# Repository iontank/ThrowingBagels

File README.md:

# ThrowingBagels
**ThrowingBagels** is a modernization of the [LEDScape](https://github.com/osresearch/LEDscape) software package. ThrowingBagels a LED driver software package for the ~~bagelbone~~ BeagleBone Black, which drives LEDs from UDP packets you yeet at it over the network, or from your own custom software.

You can use ThrowingBagels to drive up to 32 channels of individual LED strips, up to 512 LEDs per channel. Any addressable LEDs that support the WS or SK control protocols should work (WS2812, SK6812, mainly). This should work on any BeagleBone Black, running Debian Buster. 

## What's it For?

Like we said, you can drive up to 32 channels of individual LED strips, up to 512 LEDs per channel. We've used versions of this software do build things like:

<br>
<br>
<br>
If you want LEDs to blink pretty, this gives you a powerful way to control them. All images above via [Iontank](https://www.facebook.com/Iontank)'s Facebook. See also the [Iontank website](http://iontank.com).

## Installing
`curl https://raw.githubusercontent.com/iontank/ThrowingBagels/master/install.sh | bash`

This script will:

* Clone ThrowingBagels into `/opt/ThrowingBagels`
* Grant ownership of that directory to the current user (probably `debian`)
* Build the code
* Provision the Beaglebone
  * Create the leds.config file
  * Change the hostname
  * Update the `/boot/uEnv.txt` to disable HDMI and audio (we need those GPIO pins)
  * Install, but not enable, the systemd services for core applications

### Running as Services
The primary use case is going to be running this as a UDP listener, but there are a few options for running services.

The first is `bagel-launcher.service`, which simply installs the firmware and configures GPIO at boot. It's potentially useful for testing if you plan to interactively run your own software.

The second is `multidemo.service`, which runs the multidemo application (see below).

The third is the main application, `led-udp.service`, which runs the LED UDP RX program, and is the primary tool you'll likely use to control LEDs.

After install, all of these services will be installed, but none of them will be enabled.

#### Enable the Appropriate Service
For your usecase, you'll need to `sudo systemctl enable $SERVICE`, where `$SERVICE` is one of the above. You can then `sudo systemctl start $SERVICE`.

## Included Application
### PRU Firmware
The main driver of everything is the PRU Firmware, `ledscape.asm`. This is what drives the GPIO channels to activate the LEDs.

### Demo Applications
For the purposes of testing, iterating, and diagnosing hardware issues, there are several included demo applications.

* `bin/smoke`(`src/demos/smoke_test.c`): a simple smoke test application which sets the LEDs to a "soft-white" for ten seconds, and then back to black. It is the "hello world" of ThrowingBagels applications. (We don't go to full white, because that can overload many power supplies/distribution boards)
* `bin/pru_status`(`src/ledscape/pru_status.c`): a simple tool which checks the status of the PRU firmware.
* `bin/multidemo`(`src/demos/multidemo.c`): a complex and highly configurable suite of animations which run right on the BeagleBone, useful for demonstrating lighting effects without network connectivity. Great "pitch tool" to prove hardware concepts.

### LED UDP RX
The primary application, and what drives the core use-case of this software stack, is the `bin/led-udp-rx` tool (`src/net/udp-rx.c`). This tool listens on a port (default: `9999`) for frame data. This allows a powerful "render machine" to run elsewhere on the network, and send frame data to an arbitrary number of ThrowingBagels instances. See [LED UDP RX](src/net/README.md) for more details.

## Running
Included is a `launcher` script. This script configures the GPIO, deploys the firmware, and then, optionally, launches a requested binary. E.g., `./launcher bin/led-udp-rx`, would launch the LED UDP RX tool on port 9999, using `leds.config` as the source for our led configuration.

### On Configuration
Many of the tools, like `led-udp-rx` and `multidemo`, expect an LED configuration to be supplied. By default, they check `leds.config`, but they both take a command line flag to change that. The file MUST be a single line, in this format:

`number of channels,length of strips,number of bytes`

e.g.:

`32,100,4`: this would drive 32 channels of output, for strips 100 pixels long, and expects each LED to need 4 bytes (an RGBW LED). For LED UDP RX, this also sets the expected packet size- each packet should contain 50 pixels for all 32 channels (see [the UDP RX Readme](src/net/README.md) for more details).

`scripts/provision` will also prompt you for this information during the install.

## Your own ThrowingBagles software
To build your own application running on the BeagleBone, you must include two files. First, you need to include `ledstrips.h` into your C code, and you must include a LUT: either `gamma8.h` (recommended), `linear.h`, or your own custom LUT.

From there, you need to flatten your frames into a stripwise structure, e.g. you should be able to access individual pixels using `fb[(y*w)+x]` (that access the pixel at the given x/y coordinate in a 1D version of your framebuffer). See [modes.h](src/demos/modes.h) for examples.

The key methods you'll use are:

* `strip_config* leds_config(char const * filename)`: load a config file and return the strip config
* `int leds_init(strip_config *cfg)`: give a strip config, this connects to the PRU shared memory. Returns `1` on success, `0` on failure
* `void leds_draw(strip_config * cfg, const void * const frame)`: draws `frame` data to the LEDs. This needs to follow the specification above, and must be `width*height*4` bytes. This will flush the contents of the frame to the LEDs for display
* `void leds_wait(strip_config * cfg)`: wait for the LEDs to draw. You never *need* to call this, as the PRU is almost certainly flushing the data faster than your program is generating it, but *just* in case
* `void leds_close(strip_config * cfg)`: releases our hold on the PRU shared memory.

See [ledstrips.h](src/ledscape/ledstrips.h) for more details.

# ThrowingBagels Hardware
Running the software is useless if you can't plug LEDs into it. A reference design for a board [is included](pcb/README.md). It is based on designs we've used in our installations, but is strictly a *reference* design.

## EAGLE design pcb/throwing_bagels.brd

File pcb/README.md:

# Demo Board

Included in this folder is a demo board designed in Eagle. It is very impractical, and includes a library of parts. It has not been ordered and tested, so no promises. This is to illustrate pinout, and how we might use this on the hardware side.

**Hardware is provided without a warranty. 
All risk is assumed by the end user.**

### Files

- throwing_bagels.lbr - Library of parts.
- throwing_bagels.sch - Board schematic
- throwing_bagels.brd - Board layout.

### Details

This board has **4** power zones, each one containing **8** data lines. **S0-S7** are on **5V_1**, and so on. The beaglebone is powered off of **XT5** or **5V_2** depending on if you close **JP1**. The beaglebones are prone to browning out if sufficent power is not provided, this seems to knock the NIC offline first. **We do not, recommend changing the pinout of the BBB.***

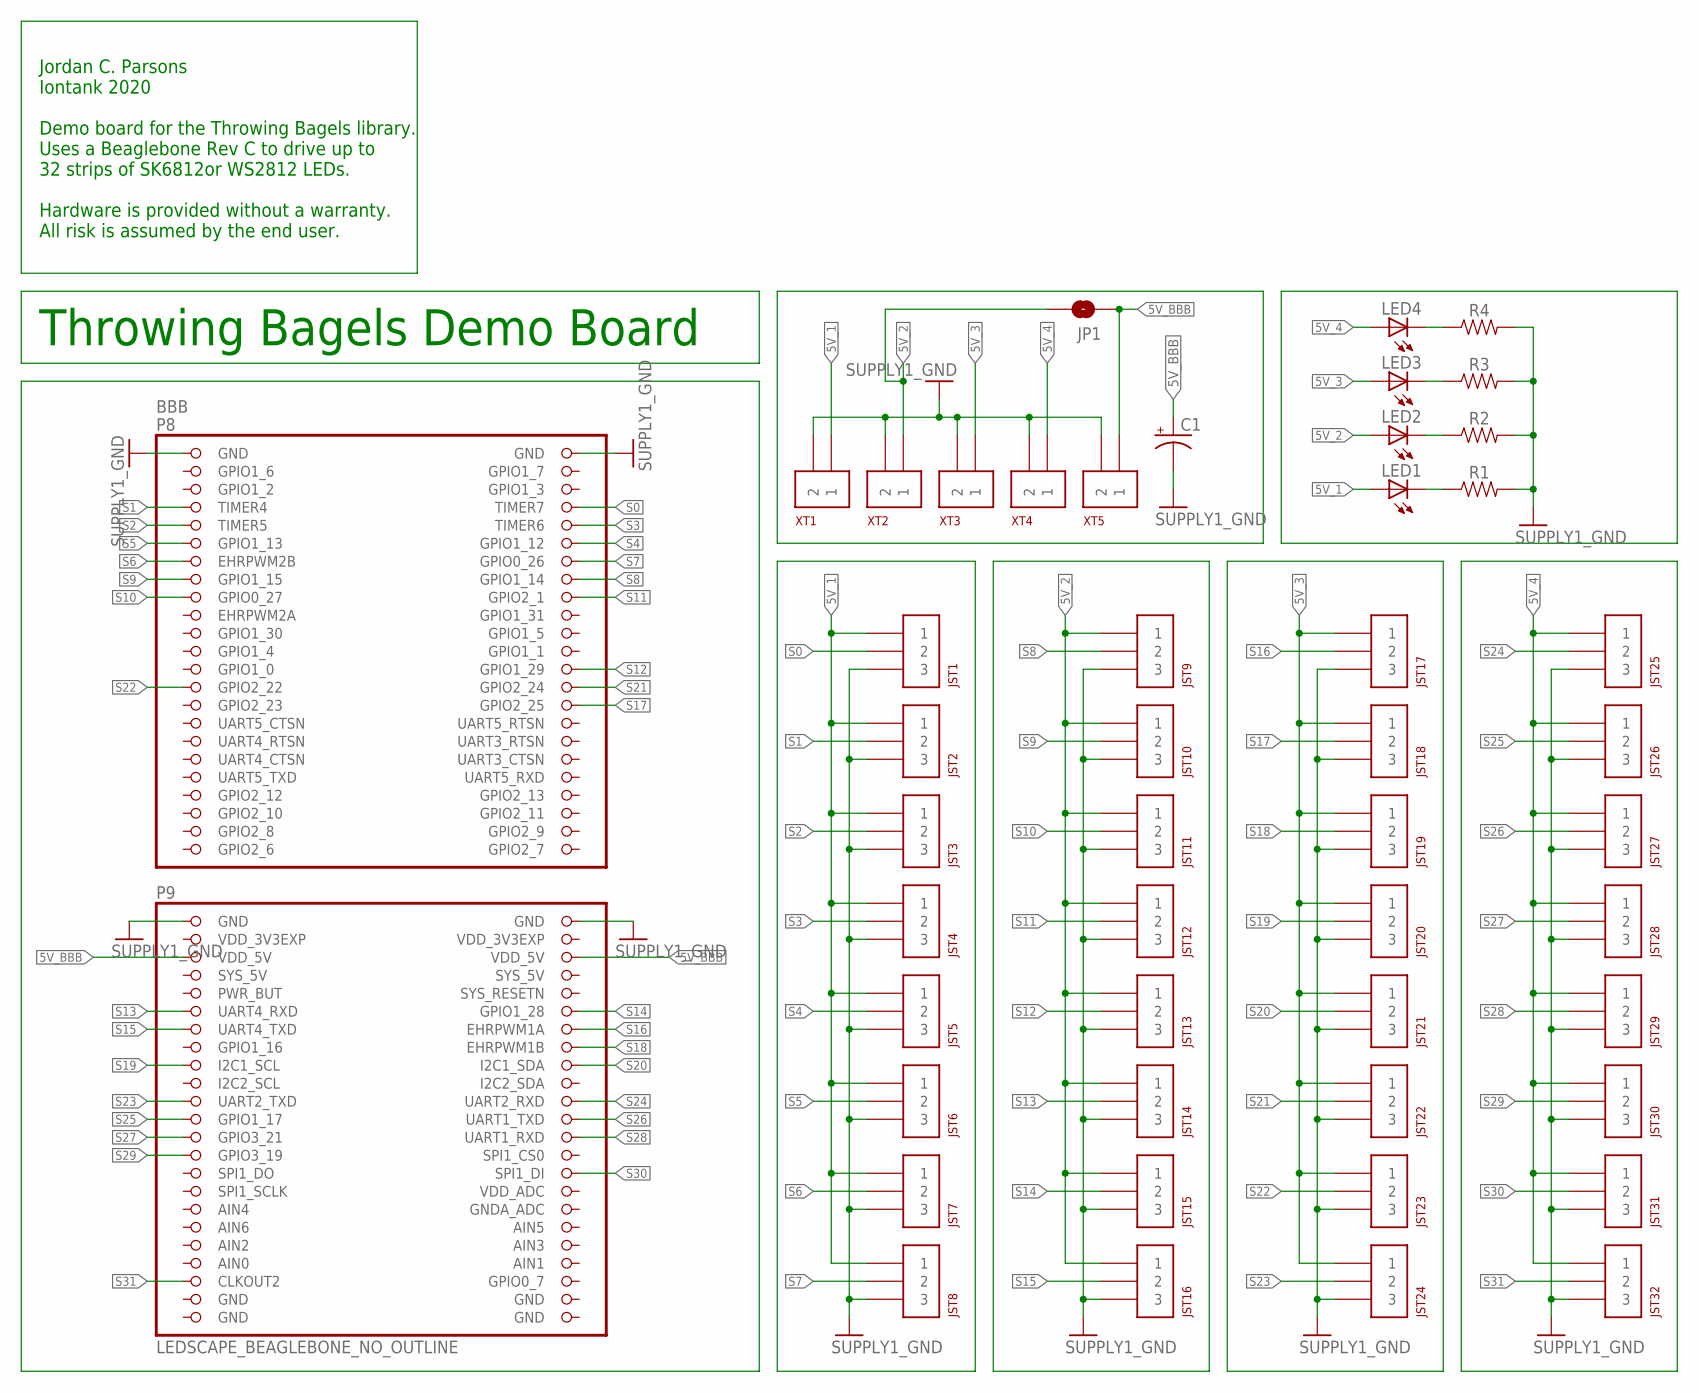
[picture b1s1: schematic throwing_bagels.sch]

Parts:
BBB: LEDSCAPE_BEAGLEBONE_NO_OUTLINE; BEAGLEBONE_SHIELD_NO_OUTLINE
C1: ADAFRUIT_CPOL-USE2,5-6E; ADAFRUIT_E2,5-6E
JP1: SPARKFUN-JUMPERS_JUMPER-SMT_2_NO_SILK; SPARKFUN-JUMPERS_SMT-JUMPER_2_NO_SILK
JST1, JST2, JST3, JST4, JST5, JST6, JST7, JST8, JST9, JST10, JST11, JST12, JST13, JST14, JST15, JST16, JST17, JST18, JST19, JST20, JST21, JST22, JST23, JST24, JST25, JST26, JST27, JST28, JST29, JST30, JST31, JST32: IONTANK-JCP_JST-XH-SIDE-3; JST-XH-SIDE-3
LED1, LED2, LED3, LED4: LEDCHIPLED_0603; CHIPLED_0603
R1, R2, R3, R4: 0603
XT1, XT2, XT3, XT4: IONTANK-JCP_XT60PWXT60PW-F20; XT60PW-F20
XT5: IONTANK-JCP_XT30PW; XT30PW-F

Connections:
5V_1: JST1.P$1 (1), JST2.P$1 (1), JST3.P$1 (1), JST4.P$1 (1), JST5.P$1 (1), JST6.P$1 (1), JST7.P$1 (1), JST8.P$1 (1), LED1.A, XT1.VCC (1)
5V_2: JP1.1, JST9.P$1 (1), JST10.P$1 (1), JST11.P$1 (1), JST12.P$1 (1), JST13.P$1 (1), JST14.P$1 (1), JST15.P$1 (1), JST16.P$1 (1), LED2.A, XT2.VCC (1)
5V_3: JST17.P$1 (1), JST18.P$1 (1), JST19.P$1 (1), JST20.P$1 (1), JST21.P$1 (1), JST22.P$1 (1), JST23.P$1 (1), JST24.P$1 (1), LED3.A, XT3.VCC (1)
5V_4: JST25.P$1 (1), JST26.P$1 (1), JST27.P$1 (1), JST28.P$1 (1), JST29.P$1 (1), JST30.P$1 (1), JST31.P$1 (1), JST32.P$1 (1), LED4.A, XT4.VCC (1)
5V_BBB: BBB.51 (VDD_5V), BBB.52 (VDD_5V), C1.+, JP1.2, XT5.POS (1)
AIN0: BBB.85 (AIN0)
GND: BBB.1 (GND), BBB.2 (GND), BBB.47 (GND), BBB.48 (GND), BBB.89 (GND), BBB.90 (GND), BBB.91 (GND), BBB.92 (GND), C1.-, JST1.P$3 (3), JST2.P$3 (3), JST3.P$3 (3), JST4.P$3 (3), JST5.P$3 (3), JST6.P$3 (3), JST7.P$3 (3), JST8.P$3 (3), JST9.P$3 (3), JST10.P$3 (3), JST11.P$3 (3), JST12.P$3 (3), JST13.P$3 (3), JST14.P$3 (3), JST15.P$3 (3), JST16.P$3 (3), JST17.P$3 (3), JST18.P$3 (3), JST19.P$3 (3), JST20.P$3 (3), JST21.P$3 (3), JST22.P$3 (3), JST23.P$3 (3), JST24.P$3 (3), JST25.P$3 (3), JST26.P$3 (3), JST27.P$3 (3), JST28.P$3 (3), JST29.P$3 (3), JST30.P$3 (3), JST31.P$3 (3), JST32.P$3 (3), R1.2, R2.2, R3.2, R4.2, XT1.GND (2), XT2.GND (2), XT3.GND (2), XT4.GND (2), XT5.NEG (2)
unnamed: LED4.C, R4.1
unnamed: LED3.C, R3.1
unnamed: LED2.C, R2.1
unnamed: LED1.C, R1.1
S0: BBB.8 (TIMER7), JST1.P$2 (2)
S1: BBB.7 (TIMER4), JST2.P$2 (2)
S2: BBB.9 (TIMER5), JST3.P$2 (2)
S3: BBB.10 (TIMER6), JST4.P$2 (2)
S4: BBB.12 (GPIO1_12), JST5.P$2 (2)
S5: BBB.11 (GPIO1_13), JST6.P$2 (2)
S6: BBB.13 (EHRPWM2B), JST7.P$2 (2)
S7: BBB.14 (GPIO0_26), JST8.P$2 (2)
S8: BBB.16 (GPIO1_14), JST9.P$2 (2)
S9: BBB.15 (GPIO1_15), JST10.P$2 (2)
S10: BBB.17 (GPIO0_27), JST11.P$2 (2)
S11: BBB.18 (GPIO2_1), JST12.P$2 (2)
S12: BBB.26 (GPIO1_29), JST13.P$2 (2)
S13: BBB.57 (UART4_RXD), JST14.P$2 (2)
S14: BBB.58 (GPIO1_28), JST15.P$2 (2)
S15: BBB.59 (UART4_TXD), JST16.P$2 (2)
S16: BBB.60 (EHRPWM1A), JST17.P$2 (2)
S17: BBB.30 (GPIO2_25), JST18.P$2 (2)
S18: BBB.62 (EHRPWM1B), JST19.P$2 (2)
S19: BBB.63 (I2C1_SCL), JST20.P$2 (2)
S20: BBB.64 (I2C1_SDA), JST21.P$2 (2)
S21: BBB.28 (GPIO2_24), JST22.P$2 (2)
S22: BBB.27 (GPIO2_22), JST23.P$2 (2)
S23: BBB.67 (UART2_TXD), JST24.P$2 (2)
S24: BBB.68 (UART2_RXD), JST25.P$2 (2)
S25: BBB.69 (GPIO1_17), JST26.P$2 (2)
S26: BBB.70 (UART1_TXD), JST27.P$2 (2)
S27: BBB.71 (GPIO3_21), JST28.P$2 (2)
S28: BBB.72 (UART1_RXD), JST29.P$2 (2)
S29: BBB.73 (GPIO3_19), JST30.P$2 (2)
S30: BBB.76 (SPI1_DI), JST31.P$2 (2)
S31: BBB.87 (CLKOUT2), JST32.P$2 (2)
SYS_5V: BBB.53 (SYS_5V)
VDD_3V3EXP: BBB.49 (VDD_3V3EXP), BBB.50 (VDD_3V3EXP)

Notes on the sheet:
Throwing Bagels Demo Board
Jordan C. Parsons Iontank 2020 Demo board for the Throwing Bagels library. Uses a Beaglebone Rev C to drive up to 32 strips of SK6812or WS2812 LEDs. Hardware is provided without a warranty. All risk is assumed by the end user.

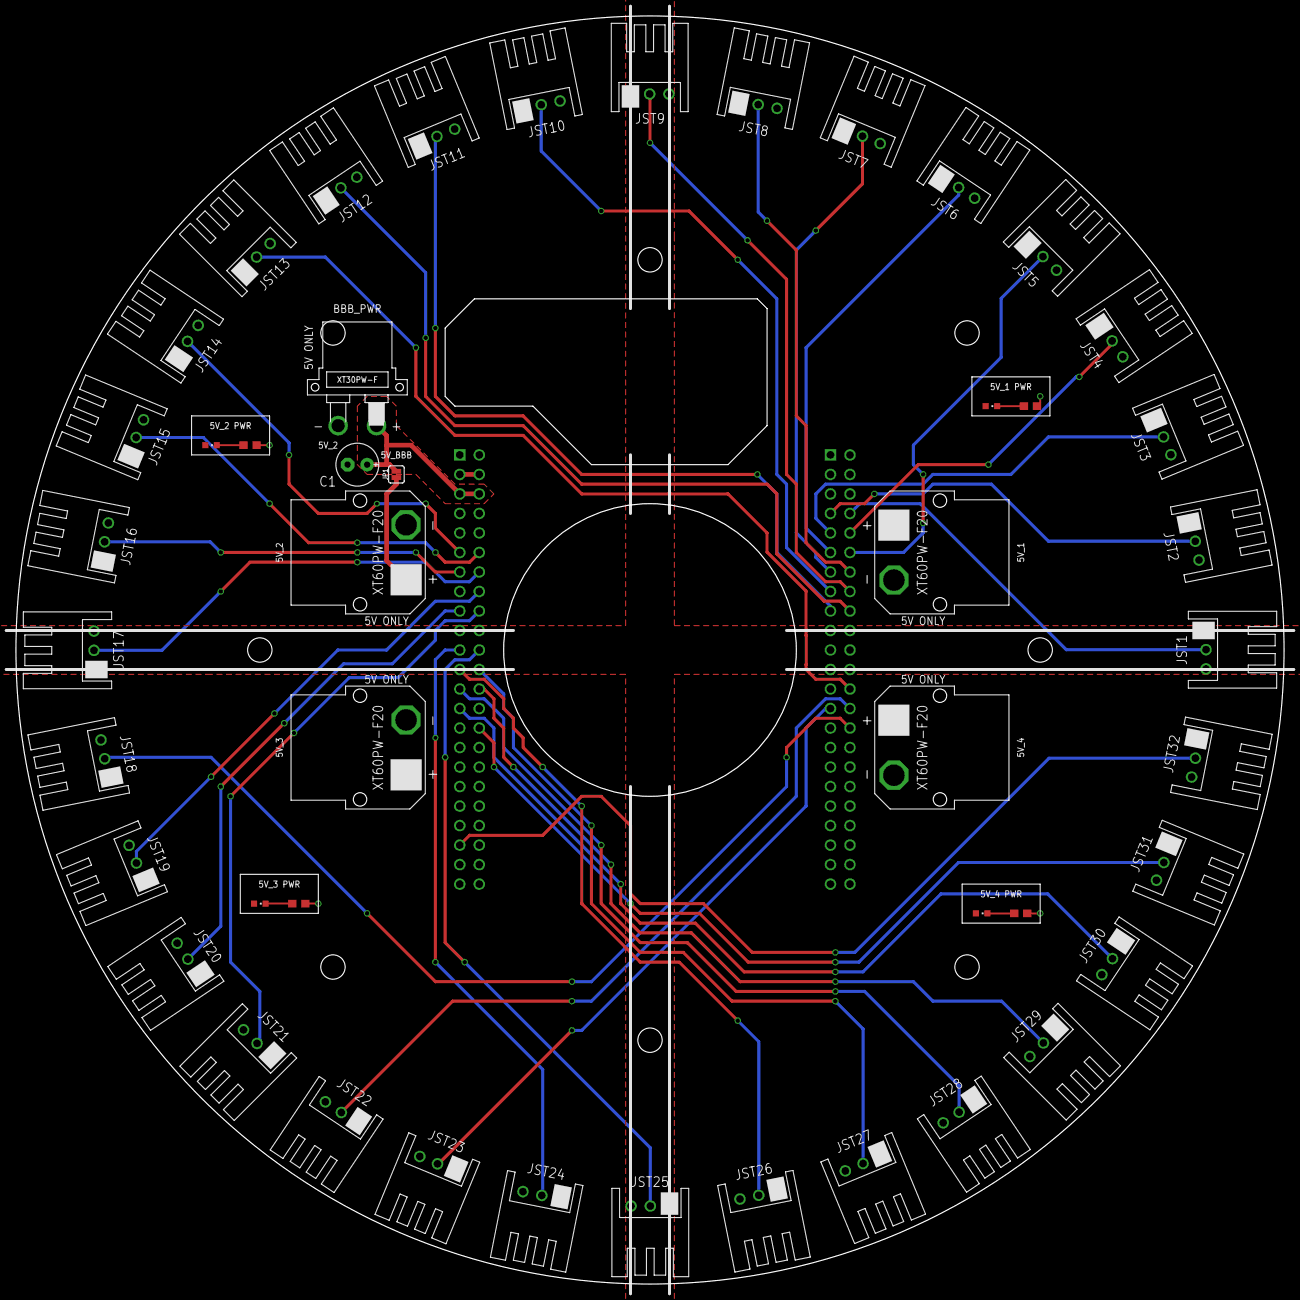
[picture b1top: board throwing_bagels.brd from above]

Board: 2 copper layers, 165.1 x 165.1 mm, 48 parts (0 on the bottom side), 43 nets.

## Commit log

2020-09-24 Initial commit, basic project layout
2020-09-29 Checkpointing a buildable (but non-working) version
2020-09-30 Smoke Test Works
    The big problem was that I wasn't actually setting the NLEDS correctly, so the PRU was just traisping off into memory to do god knows what.
    Added a PRU status checker, which scans the debug flag to determine what the PRU is up to.
2020-09-30 Added stub for a readme
2020-09-30 Multidemo Working
    Working multidemo, with a new feature: *it sets the LEDS to black when it exits*. CRAZY, RIGHT?
2020-09-30 Cleanup and Documentation
    Added documenation to most files. Cleaned up the file names, cleaned up the build process, and cleaned up some warnings.
    Everything now compiles under `-Wall` without warnings.
2020-09-30 Basic Transfer of the UDP-RX Program
    A network listener. Yay!
2020-10-01 Working UDP-RX, support tools
    Added a solid color tester program. Refined smoketest and pru-status.
    Main thing: UDP-RX now fucking works.
2020-10-01 License, improved Readmes
2020-10-07 Service Files, and a Python Demo Program
    Now deployable as a service, and a Python demo program which should be able to control plenty of Bagelbones (not threaded, so not scaleable, but that's not the point)
2020-10-07 Bagel Launcher Waits for SYSFS
    The bagel launcher service doesn't work if you run it too soon in the boot cycle, it has to be after the sysfs is mounted.
2020-10-08 Service Files Fixes
    Instead of having a set of interdepnedent services, just went the simple route of having each service file be responsible for the overall configuration of all of the components.
2020-10-08 Improved install scripts.
    This should now be a curlable install, once we have a public repo URL
2020-10-13 Bug: storing a random value instead of READING a value
    We were never actually checking the number of bytes in the input data. Whoops.
2020-10-13 Added a Memory Carveout for 512 LED long strips
    Sooooo… you can't just say "YOLO" and grab the block of memory you want just for funsies. Bad things happen if you do that.
    Thus, to avoid bad things, I've added a PRU carveout which requests the memory block in the compiled firmware. This seeeeeeems to keep the C program from running over its boundaries.
2020-10-14 Script enhancements
    There were pin-mapping issues, which this corrects. Additionally, we *do* need to explicitly disable HDMI and audio in our `uEnv` file, so this adds that to the provisioning process.
2020-10-16 Updates to provisioning script
2020-10-16 Script enhancements
2020-10-16 Incorrect service definition for MultiDemo
2020-10-16 Updating gitignore to hide unnecessary directories
2020-10-20 Significant Alterations to Memory Management
    First, instead of calcing the map size, we're just going to make the MMAPed area 128kb, which is way more than we actually need (32 channels of 512 pixels is our expected version)
    We also added a device tree, which right now needs to be manually installed. Eventually we'll add that in a script, but for now, it's a manual step.
    The device tree entry ensures that we reserve 128kb rooted at 0x80000000, which is C31 for the PRU, which is what we were hard coding our address to.
    TL;DR: this should solve our memory corruption problems.
2020-10-21 It actually tries to parse the LED config file now
    Doh, while testing, I was just using a hardcoded config. Now it actually honors your LED config.
2020-10-22 Installer Script Revisions
    The installer script now working as it should. Documentation has been brought in sync with the script. Files have been rearranged for consistency.
2020-10-27 Memory Reservations Now Actually Work
    Added a reserved block to the DTS, which *seems* to fix the problem in testing. Finally. FFS.
    Also, just for safety/security, I also added memory pinning to the LED mapping. Basically, let's ensure that our shared LED memory never gets paged out while we're using it.
    Since I was adding that, I also added an `leds_close` method, which releases the lock (and unmaps memory explicitly, instead of just letting it, uh… happen?).
2020-10-28 Minor change to pin configs
    Changed XARGS so it uses the maximum number of processes to make changes, which should help launch times.
2020-10-28 Moved all the DTS/Uboot stuff to the install script
    It was kinda dumb to have that functionality in the provision script. Now the install script fully configures the system, and you just use provision to easily change things like hostname/leds.config
2020-10-28 WAIT FOR PRU the launcher script now waits for the pru pseudofiles to be available, instead of just assuming they'll be there.
2020-10-28 Documentation Enhancements
    Also, made sure `color` binary actually closes the memory handles, to make sure we're good little programmers and clean up our mess.
2020-10-29 Base board sch.
2020-10-31 Demo board v1.0.0
2020-12-15 Memory Fixes So, something was occupying memory that I intended to use for DMA. Something still IS occupying that range, and despite lots of fighting with the device tree, I can't actually kick that 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
    So, I added a STRIP_HOP that clears that range, in addition to getting the device tree *actually* reserving the memory (save the thing we can't touch).
    Added a mem-scanner binary which helps diagnose these problems.
2020-12-17 Changing address layouts
    Fixing bugs where things don't behave correctly based on memory layout. Changed the way the ASM sets its base address, made color.c actually send multiple frames, and ditched memory locking (we're ou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
2020-12-22 Updated Pin Mapping
    The pinmap was pulling from an unitialized register because someome (me) can't count.
2020-12-22 More Pin Layout Changes
    Had to correct which register I was using to store the GPIO3 address (r31 is a control register, don't put shit in it).
    Typo in the `pin_map.asm` meant I wasn't using the correct registers for holding frame data.
    Typo in the pin_layout.txt meant one pin wasn't being addressed correctly.
2021-01-08 Cleaned up the Readme
    Added some sample images (stolen shamelessly from the Iontank FB page)
2021-01-14 Updated demo program, added pcb readme.
2021-01-22 PCB Readme fix.
2021-01-22 Minor Readme Changes
    Link to the board design, link to the LED UDP RX Readme.
2021-01-22 Correct install URL
    Moving from our private repo to the public one.
2021-01-26 Correct install URL (for real this time)
2021-01-29 Updated scripts, added zeroconf.
2021-01-29 Made cleanup harsher.
2021-02-04 Fixed W calculations for RGBW
    The initial version was doing a thing about checking the saturation and using that to drive the white content, but like, I don't need to do that complexity. This version just makes W = min(r,g,b), an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
    Suggested by this answer: https://stackoverflow.com/a/65673172
2021-02-19 Fixes Channel 29
2021-02-25 Safer register for tracking bytes
2021-03-04 Changed the Memory Map entirely
    Switched to using PRU RAM to speed up memory access. The main changes meant segmenting command RAM from frame RAM.
    This *reduces* the accumulation of errors in the output on the LEDs. It does not *solve* the problem, as sometimes fetching from memory *still* takes too long.
2021-03-09 Improved timing
2021-04-01 Performance/Timing Tweaks
    Altered the install path to update to a more recent kernel build automatically, and ensure that cpufrequtils linux-cpupower are installed.
    Those tools are used by the launcher script to disable CPU power management, which gets rid of all the flicker.

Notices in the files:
parts and their libraries:
SparkFun-Resistors: Licensing: Creative Commons ShareAlike 4.0 International - https://creativecommons.org/licenses/by-sa/4.0
